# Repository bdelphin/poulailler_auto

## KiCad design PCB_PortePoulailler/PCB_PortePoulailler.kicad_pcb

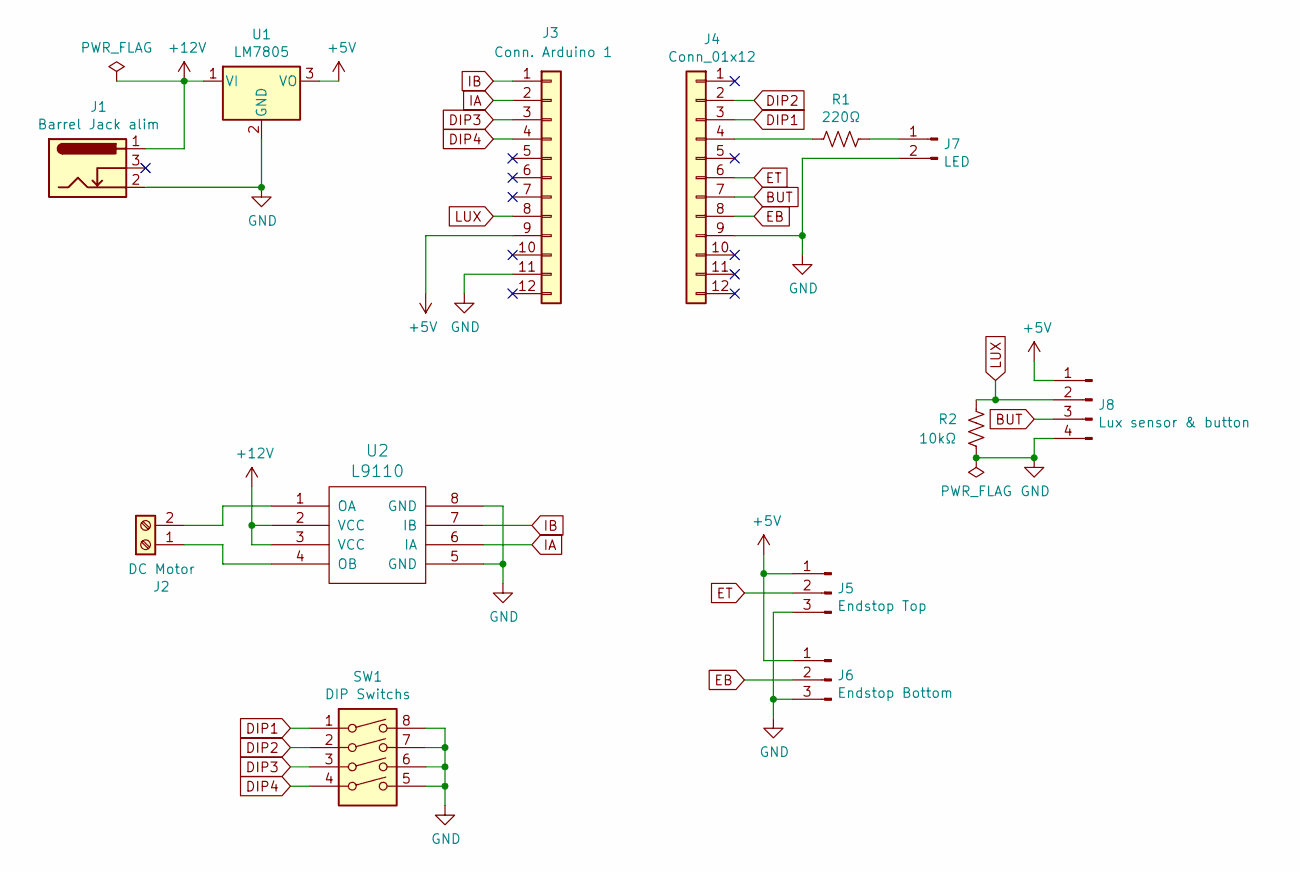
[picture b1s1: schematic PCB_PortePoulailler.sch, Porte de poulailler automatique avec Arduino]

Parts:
J1: Barrel Jack alim; BarrelJack_Horizontal
J2: DC Motor; TerminalBlock_Altech_AK300-2_P5.00mm
J3: Conn. Arduino 1; PinHeader_1x12_P2.54mm_Vertical
J4: Conn_01x12; PinHeader_1x12_P2.54mm_Vertical
J5: Endstop Top; JST_XH_B3B-XH-A_1x03_P2.50mm_Vertical
J6: Endstop Bottom; JST_XH_B3B-XH-A_1x03_P2.50mm_Vertical
J7: LED; JST_XH_B2B-XH-A_1x02_P2.50mm_Vertical
J8: Lux sensor & button; JST_XH_B4B-XH-A_1x04_P2.50mm_Vertical
R1: 220Ω; R_Axial_DIN0309_L9.0mm_D3.2mm_P12.70mm_Horizontal
R2: 10kΩ; R_Axial_DIN0309_L9.0mm_D3.2mm_P12.70mm_Horizontal
SW1: DIP Switchs; SW_DIP_SPSTx04_Slide_9.78x12.34mm_W7.62mm_P2.54mm
U1: LM7805; TO-220-3_Vertical
U2: L9110; DIP-8_W7.62mm

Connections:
+5V: J3.9, J5.1, J6.1, J8.1, U1.3 (VO)
+12V: J1.1, U1.1 (VI), U2.2 (VCC), U2.3 (VCC)
BUT: J4.7, J8.3
DIP1: J4.3, SW1.1
DIP2: J4.2, SW1.2
DIP3: J3.3, SW1.3
DIP4: J3.4, SW1.4
EB: J4.8, J6.2
ET: J4.6, J5.2
GND: J1.2, J3.11, J4.9, J5.3, J6.3, J7.2, J8.4, R2.2, SW1.5, SW1.6, SW1.7, SW1.8, U1.2 (GND), U2.5 (GND), U2.8 (GND)
IA: J3.2, U2.6 (IA)
IB: J3.1, U2.7 (IB)
LUX: J3.8, J8.2, R2.1
unnamed: J2.1, U2.4 (OB)
unnamed: J2.2, U2.1 (OA)
unnamed: J4.4, R1.1
unnamed: J7.1, R1.2

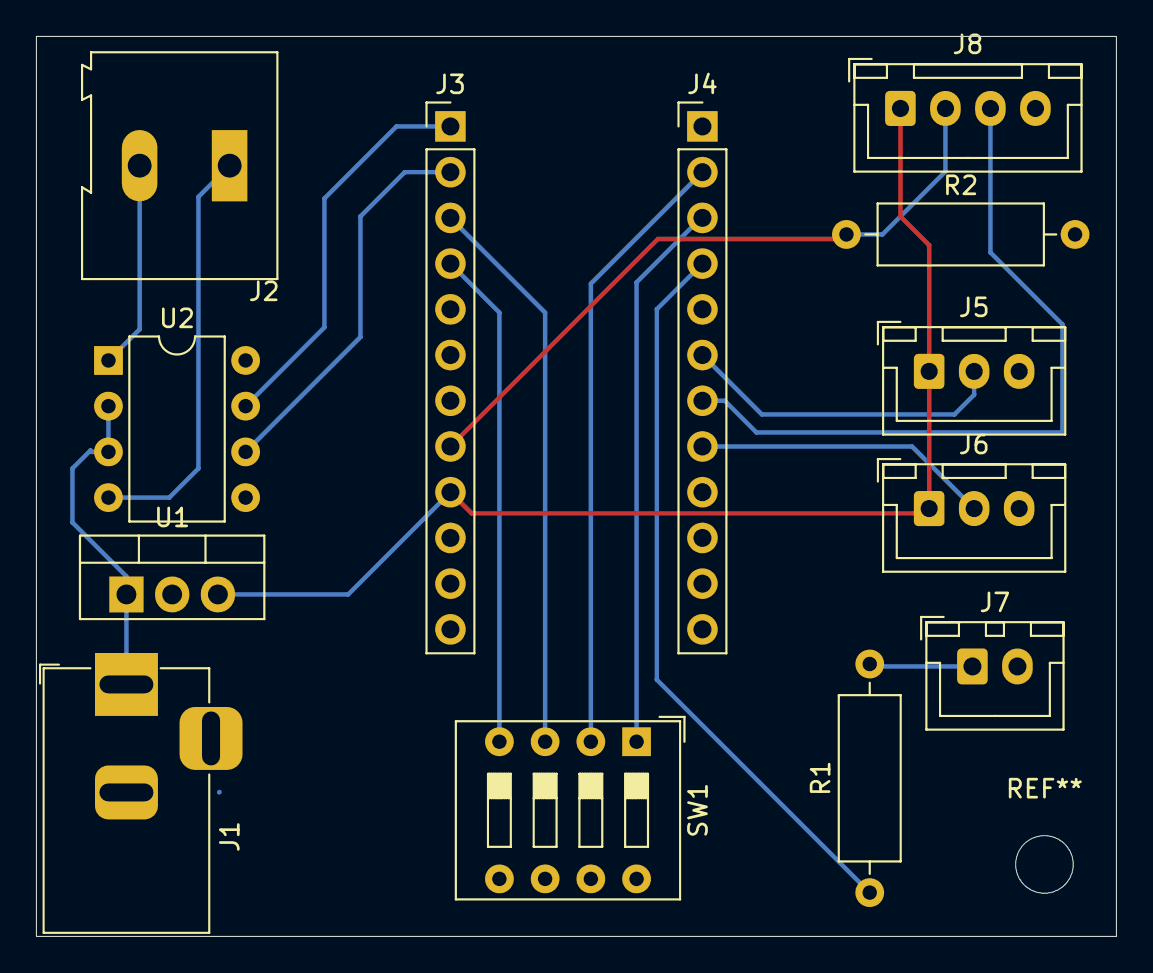
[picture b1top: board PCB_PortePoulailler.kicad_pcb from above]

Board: 2 copper layers, 60.0 x 50.0 mm, 13 parts (0 on the bottom side), 17 nets.

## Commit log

2021-07-24 PCB Kicad
2021-07-24 sketch arduino
2021-07-24 DIP switch configuration added
2021-07-26 added close crash detection & manual override
2021-07-26 FR documentation added
2021-07-27 new motor driver : L298N
2021-07-27 documentation updated
2021-07-27 doc updated
